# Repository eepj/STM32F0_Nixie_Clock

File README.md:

# STM32F0_Nixie_Clock
An STM32 nixie clock project.

## Disclaimer
High DC voltages can cause severe injuries or death. Proceed at your own risk.

## Hardware 
### Files
* [KiCad project](./Hardware/STM32F0_Nixie_Clock.pro)
* [Schematics](./Hardware/STM32F0_Nixie_Clock.pdf)
* [Gerber](./main/Hardware/Gerber)

### Parts
Refer to [BOM](./Hardware/STM32F0_Nixie_Clock_BOM.xlsx):
* [STM32F042F6 core](https://www.st.com/resource/en/datasheet/stm32f042f6.pdf)
* [MAX1771 step-up driver](https://datasheets.maximintegrated.com/en/ds/MAX1771.pdf)
* [DS3231 I2C RTC](https://www.maximintegrated.com/en/products/analog/real-time-clocks/DS3231.html)
* [HV5222 32-channel open-drain serial-to-parallel converter](https://ww1.microchip.com/downloads/en/DeviceDoc/20005418B.pdf)

## Firmware
### Programs
* Main program: [`main.c`](./Firmware/Core/Src/main.c)
* Interrupts: [`stm32f0xx_it.c`](/Firmware/Core/Src/stm32f0xx_it.c)

### Custom libraries
* HV5222 driver: [`nixie.h`](./Firmware/Core/Src/lib/sr)
* DS3231 driver: [`ds3231_for_stm32_hal.h`](https://github.com/eepj/ds3231_for_stm32_hal)

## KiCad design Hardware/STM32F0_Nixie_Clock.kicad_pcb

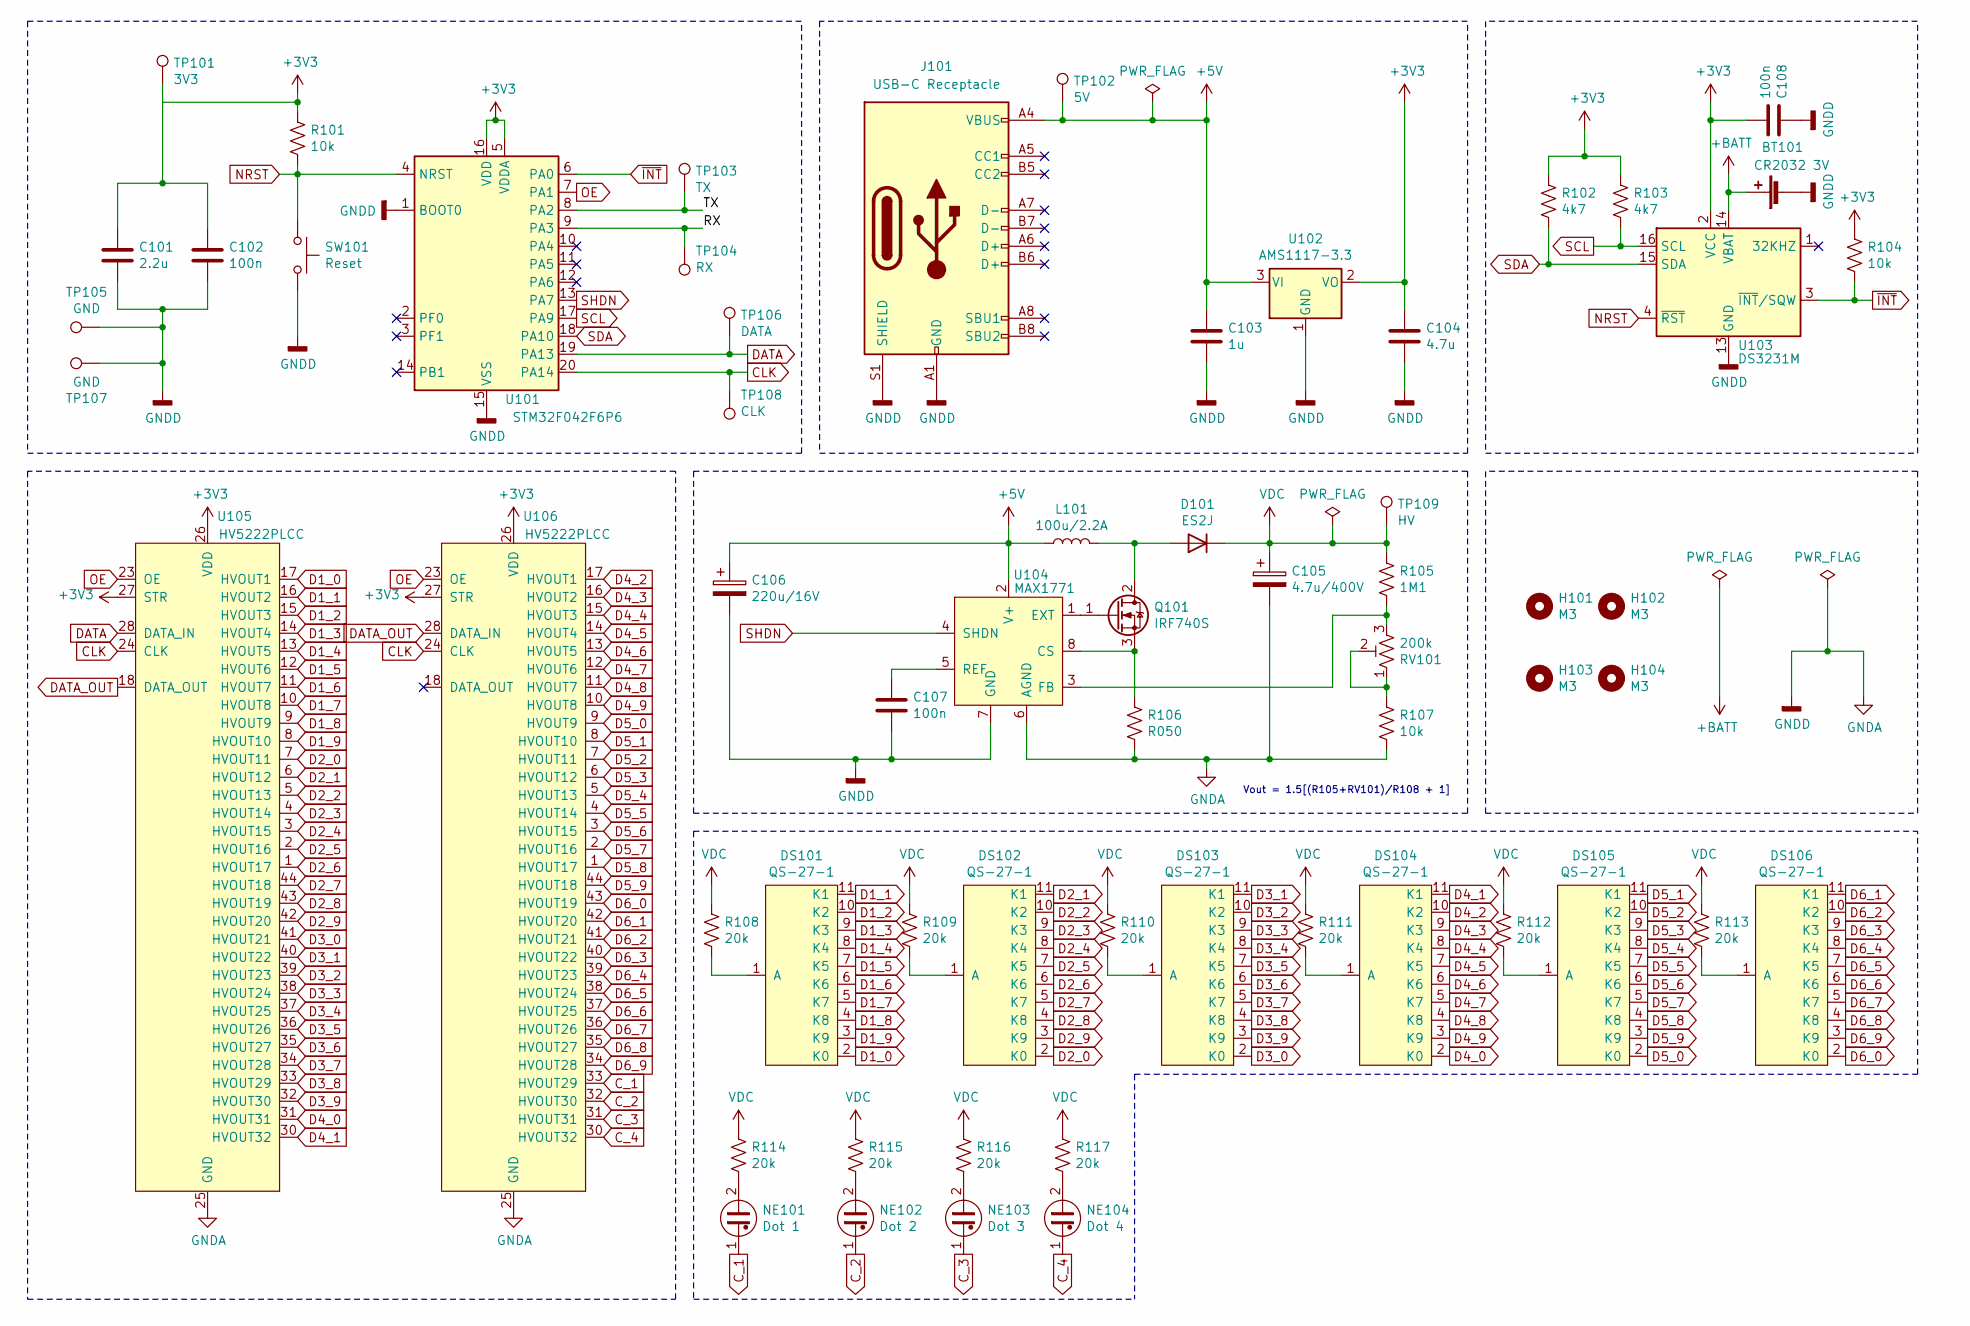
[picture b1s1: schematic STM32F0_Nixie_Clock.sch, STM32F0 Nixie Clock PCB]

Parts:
BT101: CR2032 3V; BatteryHolder_Keystone_1060_1x2032
C101: 2.2u; C_0603_1608Metric_Pad1.05x0.95mm_HandSolder
C102, C107, C108: 100n; C_0603_1608Metric_Pad1.05x0.95mm_HandSolder
C103: 1u; C_1206_3216Metric_Pad1.42x1.75mm_HandSolder
C104: 4.7u; C_1210_3225Metric_Pad1.42x2.65mm_HandSolder
C105: 4.7u/400V; CP_Elec_8x10.5
C106: 220u/16V; CP_Elec_6.3x7.7
D101: ES2J; D_SMA_Handsoldering
DS101, DS102, DS103, DS104, DS105, DS106: QS-27-1; JST_PH_B11B-PH-K_1x11_P2.00mm_Vertical
H101, H102, H103, H104: M3; MountingHole_3.2mm_M3
J101: USB-C Receptacle; USB_C_Receptacle_HRO_TYPE-C-31-M-12
L101: 100u/2.2A; L_12x12mm_H8mm
NE101: Dot 1; JST_PH_B2B-PH-K_1x02_P2.00mm_Vertical
NE102: Dot 2; JST_PH_B2B-PH-K_1x02_P2.00mm_Vertical
NE103: Dot 3; JST_PH_B2B-PH-K_1x02_P2.00mm_Vertical
NE104: Dot 4; JST_PH_B2B-PH-K_1x02_P2.00mm_Vertical
Q101: IRF740S; TO-263-2
R101, R104, R107: 10k; R_0603_1608Metric_Pad1.05x0.95mm_HandSolder
R102, R103: 4k7; R_0603_1608Metric_Pad1.05x0.95mm_HandSolder
R105: 1M1; R_0603_1608Metric_Pad1.05x0.95mm_HandSolder
R106: R050; R_2512_6332Metric_Pad1.52x3.35mm_HandSolder
R108, R109, R110, R111, R112, R113, R114, R115, R116, R117: 20k; R_0603_1608Metric_Pad1.05x0.95mm_HandSolder
RV101: 200k; Potentiometer_Vishay_T73YP_Vertical
SW101: Reset; SW_SPST_TL3342
TP101: 3V3; TestPoint_Pad_D1.5mm
TP102: 5V; TestPoint_Pad_D1.5mm
TP103: TX; TestPoint_Pad_D1.5mm
TP104: RX; TestPoint_Pad_D1.5mm
TP105, TP107: GND; TestPoint_Pad_D1.5mm
TP106: DATA; TestPoint_Pad_D1.5mm
TP108: CLK; TestPoint_Pad_D1.5mm
TP109: HV; TestPoint_Pad_1.0x1.0mm
U101: STM32F042F6P6; TSSOP-20_4.4x6.5mm_P0.65mm
U102: AMS1117-3.3; SOT-223-3_TabPin2
U103: DS3231M; SOIC-16W_7.5x10.3mm_P1.27mm
U104: MAX1771; SO-8_3.9x4.9mm_P1.27mm
U105, U106: HV5222PLCC; PLCC-44_16.6x16.6mm_P1.27mm

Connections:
+3V3: C101.1, C102.1, C104.1, C108.2, R101.1, R102.1, R103.1, R104.1, TP101.1, U101.5 (VDDA), U101.16 (VDD), U102.2 (VO), U103.2 (VCC), U105.26 (VDD), U105.27 (STR), U106.26 (VDD), U106.27 (STR)
+5V: C103.1, C106.1, J101.A4 (VBUS), J101.A9 (VBUS), J101.B4 (VBUS), J101.B9 (VBUS), L101.1, TP102.1, U102.3 (VI), U104.2 (V+)
+BATT: BT101.1 (+), U103.14 (VBAT)
/RX: TP104.1, U101.9 (PA3)
/TX: TP103.1, U101.8 (PA2)
CLK: TP108.1, U101.20 (PA14), U105.24 (CLK), U106.24 (CLK)
C_1: NE101.1, U106.33 (HVOUT29)
C_2: NE102.1, U106.32 (HVOUT30)
C_3: NE103.1, U106.31 (HVOUT31)
C_4: NE104.1, U106.30 (HVOUT32)
D1_0: DS101.2 (K0), U105.17 (HVOUT1)
D1_1: DS101.11 (K1), U105.16 (HVOUT2)
D1_2: DS101.10 (K2), U105.15 (HVOUT3)
D1_3: DS101.9 (K3), U105.14 (HVOUT4)
D1_4: DS101.8 (K4), U105.13 (HVOUT5)
D1_5: DS101.7 (K5), U105.12 (HVOUT6)
D1_6: DS101.6 (K6), U105.11 (HVOUT7)
D1_7: DS101.5 (K7), U105.10 (HVOUT8)
D1_8: DS101.4 (K8), U105.9 (HVOUT9)
D1_9: DS101.3 (K9), U105.8 (HVOUT10)
D2_0: DS102.2 (K0), U105.7 (HVOUT11)
D2_1: DS102.11 (K1), U105.6 (HVOUT12)
D2_2: DS102.10 (K2), U105.5 (HVOUT13)
D2_3: DS102.9 (K3), U105.4 (HVOUT14)
D2_4: DS102.8 (K4), U105.3 (HVOUT15)
D2_5: DS102.7 (K5), U105.2 (HVOUT16)
D2_6: DS102.6 (K6), U105.1 (HVOUT17)
D2_7: DS102.5 (K7), U105.44 (HVOUT18)
D2_8: DS102.4 (K8), U105.43 (HVOUT19)
D2_9: DS102.3 (K9), U105.42 (HVOUT20)
D3_0: DS103.2 (K0), U105.41 (HVOUT21)
D3_1: DS103.11 (K1), U105.40 (HVOUT22)
D3_2: DS103.10 (K2), U105.39 (HVOUT23)
D3_3: DS103.9 (K3), U105.38 (HVOUT24)
D3_4: DS103.8 (K4), U105.37 (HVOUT25)
D3_5: DS103.7 (K5), U105.36 (HVOUT26)
D3_6: DS103.6 (K6), U105.35 (HVOUT27)
D3_7: DS103.5 (K7), U105.34 (HVOUT28)
D3_8: DS103.4 (K8), U105.33 (HVOUT29)
D3_9: DS103.3 (K9), U105.32 (HVOUT30)
D4_0: DS104.2 (K0), U105.31 (HVOUT31)
D4_1: DS104.11 (K1), U105.30 (HVOUT32)
D4_2: DS104.10 (K2), U106.17 (HVOUT1)
D4_3: DS104.9 (K3), U106.16 (HVOUT2)
D4_4: DS104.8 (K4), U106.15 (HVOUT3)
D4_5: DS104.7 (K5), U106.14 (HVOUT4)
D4_6: DS104.6 (K6), U106.13 (HVOUT5)
D4_7: DS104.5 (K7), U106.12 (HVOUT6)
D4_8: DS104.4 (K8), U106.11 (HVOUT7)
D4_9: DS104.3 (K9), U106.10 (HVOUT8)
D5_0: DS105.2 (K0), U106.9 (HVOUT9)
D5_1: DS105.11 (K1), U106.8 (HVOUT10)
D5_2: DS105.10 (K2), U106.7 (HVOUT11)
D5_3: DS105.9 (K3), U106.6 (HVOUT12)
D5_4: DS105.8 (K4), U106.5 (HVOUT13)
D5_5: DS105.7 (K5), U106.4 (HVOUT14)
D5_6: DS105.6 (K6), U106.3 (HVOUT15)
D5_7: DS105.5 (K7), U106.2 (HVOUT16)
D5_8: DS105.4 (K8), U106.1 (HVOUT17)
D5_9: DS105.3 (K9), U106.44 (HVOUT18)
D6_0: DS106.2 (K0), U106.43 (HVOUT19)
D6_1: DS106.11 (K1), U106.42 (HVOUT20)
D6_2: DS106.10 (K2), U106.41 (HVOUT21)
D6_3: DS106.9 (K3), U106.40 (HVOUT22)
D6_4: DS106.8 (K4), U106.39 (HVOUT23)
D6_5: DS106.7 (K5), U106.38 (HVOUT24)
D6_6: DS106.6 (K6), U106.37 (HVOUT25)
D6_7: DS106.5 (K7), U106.36 (HVOUT26)
D6_8: DS106.4 (K8), U106.35 (HVOUT27)
D6_9: DS106.3 (K9), U106.34 (HVOUT28)
DATA: TP106.1, U101.19 (PA13), U105.28 (DATA_IN)
DATA_OUT: U105.18 (DATA_OUT), U106.28 (DATA_IN)
GNDA: BT101.2 (-), C101.2, C102.2, C103.2, C104.2, C105.2, C106.2, C107.2, C108.1, J101.A1 (GND), J101.A12 (GND), J101.B1 (GND), J101.B12 (GND), J101.S1 (SHIELD), R106.2, R107.2, SW101.2, TP105.1, TP107.1, U101.1 (BOOT0), U101.15 (VSS), U102.1 (GND), U103.5 (GND), U103.6 (GND), U103.7 (GND), U103.8 (GND), U103.9 (GND), U103.10 (GND), U103.11 (GND), U103.12 (GND), U103.13 (GND), U104.6 (AGND), U104.7 (GND), U105.25 (GND), U106.25 (GND)
NRST: R101.2, SW101.1, U101.4 (NRST), U103.4 (~RST)
unnamed: C107.1, U104.5 (REF)
unnamed: D101.2 (A), L101.2, Q101.2 (D)
unnamed: DS101.1 (A), R108.2
unnamed: DS102.1 (A), R109.2
unnamed: DS103.1 (A), R110.2
unnamed: DS104.1 (A), R111.2
unnamed: DS105.1 (A), R112.2
unnamed: DS106.1 (A), R113.2
unnamed: NE101.2, R114.2
unnamed: NE102.2, R115.2
unnamed: NE103.2, R116.2
unnamed: NE104.2, R117.2
unnamed: Q101.1 (G), U104.1 (EXT)
unnamed: Q101.3 (S), R106.1, U104.8 (CS)
unnamed: R105.2, RV101.3, U104.3 (FB)
unnamed: R107.1, RV101.1, RV101.2
OE: U101.7 (PA1), U105.23 (OE), U106.23 (OE)
SCL: R103.2, U101.17 (PA9), U103.16 (SCL)
SDA: R102.2, U101.18 (PA10), U103.15 (SDA)
SHDN: U101.13 (PA7), U104.4 (SHDN)
VDC: C105.1, D101.1 (K), R105.1, R108.1, R109.1, R110.1, R111.1, R112.1, R113.1, R114.1, R115.1, R116.1, R117.1, TP109.1
~INT: R104.2, U101.6 (PA0), U103.3 (~INT~/SQW)

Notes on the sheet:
Vout = 1.5[(R105+RV101)/R108 + 1]

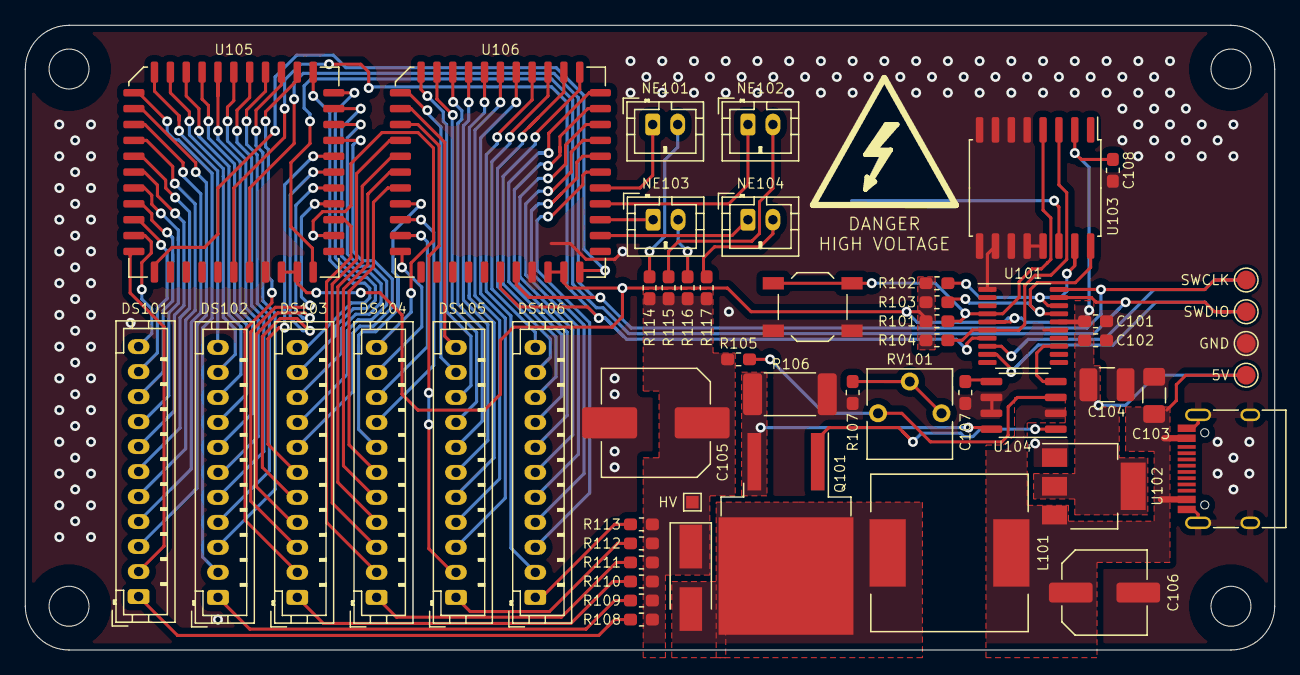
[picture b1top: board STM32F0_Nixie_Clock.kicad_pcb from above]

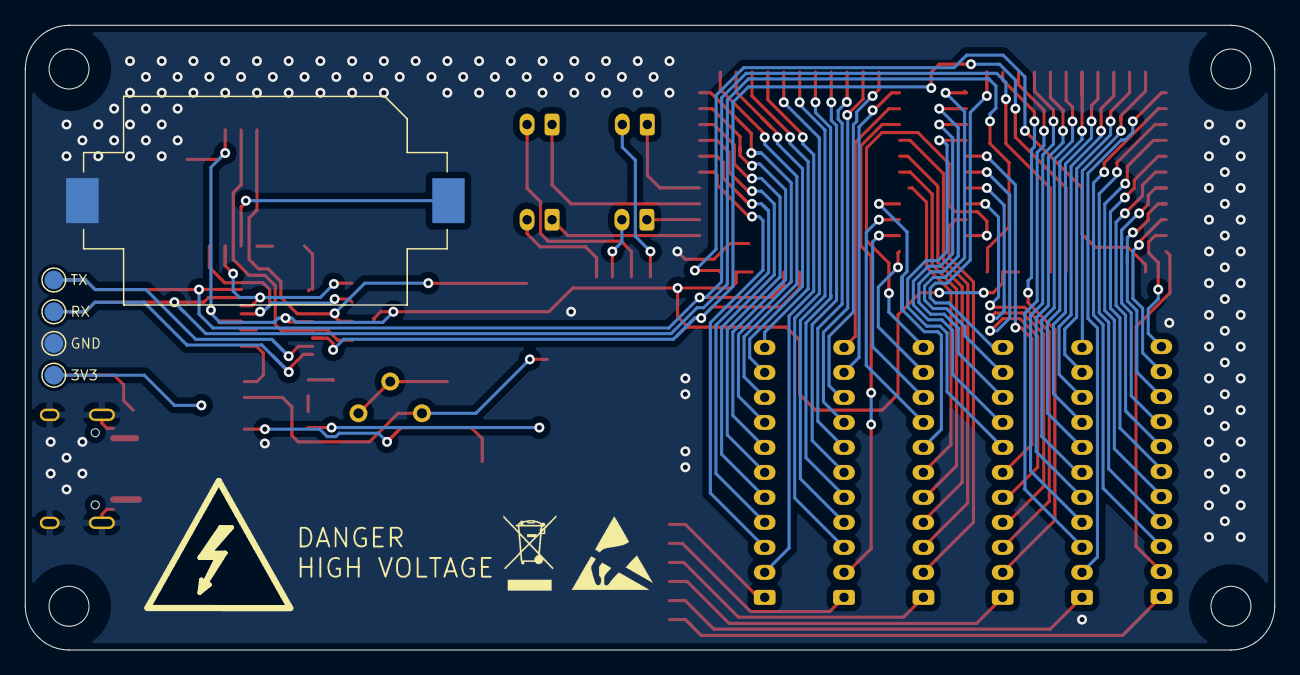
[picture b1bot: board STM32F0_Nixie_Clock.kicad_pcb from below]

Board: 2 copper layers, 100.0 x 50.0 mm, 61 parts (5 on the bottom side), 96 nets.

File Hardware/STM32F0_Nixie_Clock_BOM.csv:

Designator,Value,Footprint
    BT101,CR2032 3V,Battery:BatteryHolder_Keystone_1060_1x2032
    C101,2.2u,Capacitor_SMD:C_0603_1608Metric_Pad1.05x0.95mm_HandSolder
    C102,100n,Capacitor_SMD:C_0603_1608Metric_Pad1.05x0.95mm_HandSolder
    C103,1u,Capacitor_SMD:C_1206_3216Metric_Pad1.42x1.75mm_HandSolder
    C104,4.7u,Capacitor_SMD:C_1210_3225Metric_Pad1.42x2.65mm_HandSolder
    C105,4.7u/400V,Capacitor_SMD:CP_Elec_8x10.5
    C106,220u/16V,Capacitor_SMD:CP_Elec_6.3x7.7
    C107,100n,Capacitor_SMD:C_0603_1608Metric_Pad1.05x0.95mm_HandSolder
    C108,100n,Capacitor_SMD:C_0603_1608Metric_Pad1.05x0.95mm_HandSolder
    D101,ES2J,Diode_SMD:D_SMA_Handsoldering
    DS101,JST PH 2.0mm 11P,Connector_JST:JST_PH_B11B-PH-K_1x11_P2.00mm_Vertical
    DS102,JST PH 2.0mm 11P,Connector_JST:JST_PH_B11B-PH-K_1x11_P2.00mm_Vertical
    DS103,JST PH 2.0mm 11P,Connector_JST:JST_PH_B11B-PH-K_1x11_P2.00mm_Vertical
    DS104,JST PH 2.0mm 11P,Connector_JST:JST_PH_B11B-PH-K_1x11_P2.00mm_Vertical
    DS105,JST PH 2.0mm 11P,Connector_JST:JST_PH_B11B-PH-K_1x11_P2.00mm_Vertical
    DS106,JST PH 2.0mm 11P,Connector_JST:JST_PH_B11B-PH-K_1x11_P2.00mm_Vertical
    J101,USB-C Receptacle,Connector_USB:USB_C_Receptacle_HRO_TYPE-C-31-M-12
    L101,100u/2.2A,Inductor_SMD:L_12x12mm_H8mm
    NE101,Dot 1,Connector_JST:JST_PH_B2B-PH-K_1x02_P2.00mm_Vertical
    NE102,Dot 2,Connector_JST:JST_PH_B2B-PH-K_1x02_P2.00mm_Vertical
    NE103,Dot 3,Connector_JST:JST_PH_B2B-PH-K_1x02_P2.00mm_Vertical
    NE104,Dot 4,Connector_JST:JST_PH_B2B-PH-K_1x02_P2.00mm_Vertical
    Q101,IRF740S,Package_TO_SOT_SMD:TO-263-2
    R101,10k,Resistor_SMD:R_0603_1608Metric_Pad1.05x0.95mm_HandSolder
    R102,4k7,Resistor_SMD:R_0603_1608Metric_Pad1.05x0.95mm_HandSolder
    R103,4k7,Resistor_SMD:R_0603_1608Metric_Pad1.05x0.95mm_HandSolder
    R104,10k,Resistor_SMD:R_0603_1608Metric_Pad1.05x0.95mm_HandSolder
    R105,1M1,Resistor_SMD:R_0603_1608Metric_Pad1.05x0.95mm_HandSolder
    R106,R050,Resistor_SMD:R_2512_6332Metric_Pad1.52x3.35mm_HandSolder
    R107,10k,Resistor_SMD:R_0603_1608Metric_Pad1.05x0.95mm_HandSolder
    R108,20k,Resistor_SMD:R_0603_1608Metric_Pad1.05x0.95mm_HandSolder
    R109,20k,Resistor_SMD:R_0603_1608Metric_Pad1.05x0.95mm_HandSolder
    R110,20k,Resistor_SMD:R_0603_1608Metric_Pad1.05x0.95mm_HandSolder
    R111,20k,Resistor_SMD:R_0603_1608Metric_Pad1.05x0.95mm_HandSolder
    R112,20k,Resistor_SMD:R_0603_1608Metric_Pad1.05x0.95mm_HandSolder
    R113,20k,Resistor_SMD:R_0603_1608Metric_Pad1.05x0.95mm_HandSolder
    R114,20k,Resistor_SMD:R_0603_1608Metric_Pad1.05x0.95mm_HandSolder
    R115,20k,Resistor_SMD:R_0603_1608Metric_Pad1.05x0.95mm_HandSolder
    R116,20k,Resistor_SMD:R_0603_1608Metric_Pad1.05x0.95mm_HandSolder
    R117,20k,Resistor_SMD:R_0603_1608Metric_Pad1.05x0.95mm_HandSolder
    RV101,200k,Potentiometer_THT:Potentiometer_Vishay_T73YP_Vertical
    SW101,TL3342,Button_Switch_SMD:SW_SPST_TL3342
    U101,STM32F042F6P6,Package_SO:TSSOP-20_4.4x6.5mm_P0.65mm
    U102,AMS1117-3.3,Package_TO_SOT_SMD:SOT-223-3_TabPin2
    U103,DS3231M,Package_SO:SOIC-16W_7.5x10.3mm_P1.27mm
    U104,MAX1771,Package_SO:SO-8_3.9x4.9mm_P1.27mm
    U105,HV5222PLCC,Package_LCC:PLCC-44_16.6x16.6mm_P1.27mm
    U106,HV5222PLCC,Package_LCC:PLCC-44_16.6x16.6mm_P1.27mm

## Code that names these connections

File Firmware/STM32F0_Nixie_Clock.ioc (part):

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Mcu.Name=STM32F042F6Px
Mcu.Package=TSSOP20
Mcu.UserName=STM32F042F6Px
PA0.GPIOParameters=GPIO_Label,GPIO_ModeDefaultEXTI
PA0.GPIO_Label=INT
PA0.GPIO_ModeDefaultEXTI=GPIO_MODE_IT_FALLING
PA0.Signal=GPXTI0
PA1.GPIOParameters=GPIO_Label
PA1.GPIO_Label=OE
PA1.Signal=GPIO_Output
PA10.Mode=I2C
PA10.Signal=I2C1_SDA
PA13.GPIOParameters=GPIO_Label
PA13.GPIO_Label=DATA
PA13.Signal=GPIO_Output
PA14.GPIOParameters=GPIO_Label
PA14.GPIO_Label=CLK
PA14.Signal=GPIO_Output
PA2.Mode=Asynchronous
PA2.Signal=USART2_TX
PA3.Mode=Asynchronous
PA3.Signal=USART2_RX
PA7.GPIOParameters=GPIO_Label
PA7.GPIO_Label=SHDN
PA7.Signal=GPIO_Output
PA9.Mode=I2C
PA9.Signal=I2C1_SCL
board=custom

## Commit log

2021-01-24 Add STM32CubeMX project
2021-01-24 Add pin assignment and configuration
2021-01-24 Modify pin assignment
2021-01-24 Add libraries
2021-01-24 Add HV5222 control functions
2021-01-24 Format main.c
2021-01-24 Format all files
2021-01-24 Undo line wrap
2021-01-24 Import version 3.0 PCB KiCad project
2021-01-24 Update schematics PDF
2021-01-25 Change delay function name
2021-01-25 Update putchar function return condition
2021-01-26 Update alarm checkin condition
2021-01-26 Clean up brackets
2021-01-29 Add decoupling decapacitor to RTC
2021-01-29 Plot gerber
2021-03-27 Replace USB-C receptacle symbol
2021-04-11 Repository restructure
2021-04-11 Resturcture repository
